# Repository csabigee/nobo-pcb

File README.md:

# nobo-pcb
PCB design files for the nobo thermostat

Designed in KiCad

very simple schematic:

https://github.com/csabigee/nobo-pcb/assets/96885207/b5cf36cf-c3b2-4169-932b-3addc52b22ec

Links:
------------------------
 
[:mag: Reverse engineering the protocol :mag_right:](https://github.com/csabigee/nobo/wiki/Home)

[:hammer_and_wrench: Building the custom thermostat :hammer_and_wrench:](https://www.hackster.io/csabigee/nobo-wireless-thermostat-01f106)

[:zap: PCB design files :zap:](https://github.com/csabigee/nobo-pcb)

[:gift: Enclosure design files :gift:](https://github.com/csabigee/nobo-enclosure)

[:octocat: Software sources :octocat:](https://github.com/csabigee/nobo)

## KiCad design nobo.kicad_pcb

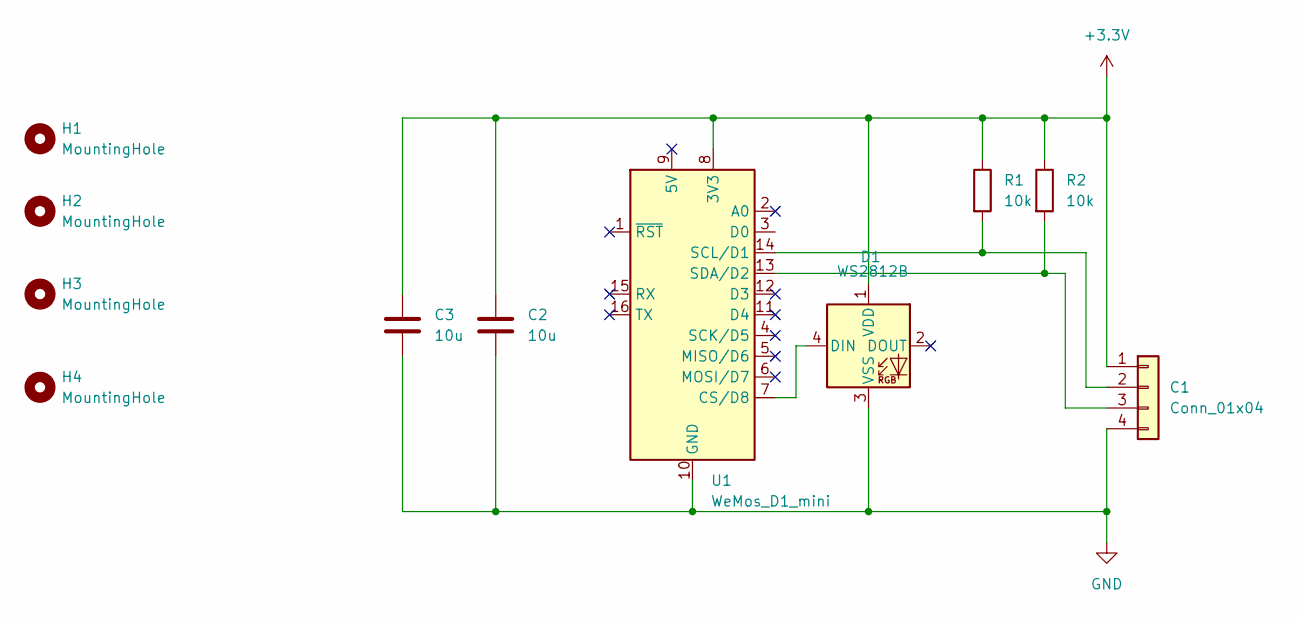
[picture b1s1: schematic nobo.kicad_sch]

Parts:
C1: Conn_01x04; nobo
C2, C3: 10u; C_0603_1608Metric_Pad1.08x0.95mm_HandSolder
D1: WS2812B; LED_WS2812B_PLCC4_5.0x5.0mm_P3.2mm
H1, H2, H3, H4: MountingHole; MountingHole_3.7mm
R1, R2: 10k; R_0603_1608Metric_Pad0.98x0.95mm_HandSolder
U1: WeMos_D1_mini; WEMOS_D1_mini_light2

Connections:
+3.3V: C1.1 (Pin_1_(3.3V)), C2.1, C3.1, D1.1 (VDD), R1.1, R2.1, U1.8 (3V3); also elsewhere on the board
GND: C1.4 (Pin_4_(GND)), C2.2, C3.2, D1.3 (VSS), U1.10 (GND); also elsewhere on the board
unnamed 2: C1.2 (Pin_2_(SCL)), R1.2, U1.14 (SCL/D1); also elsewhere on the board
unnamed 3: C1.3 (Pin_3_(SDA)), R2.2, U1.13 (SDA/D2); also elsewhere on the board
unnamed: D1.4 (DIN), U1.7 (CS/D8)

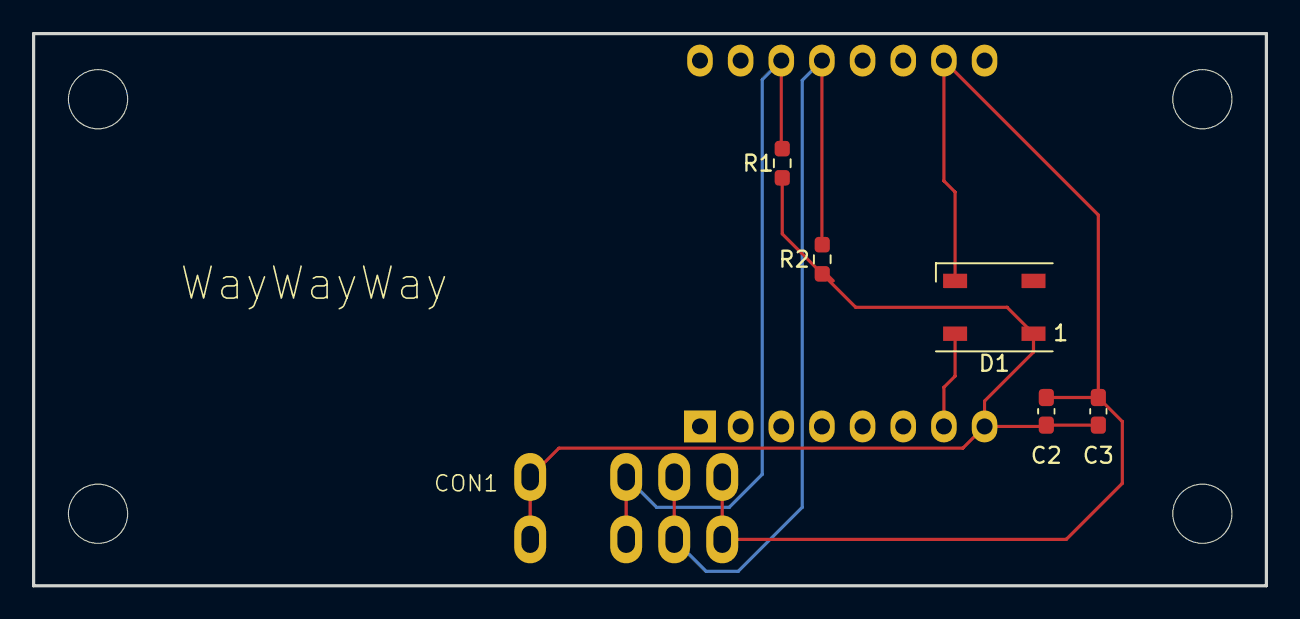
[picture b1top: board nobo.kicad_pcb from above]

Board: 2 copper layers, 77.0 x 34.5 mm, 11 parts (1 on the bottom side), 5 nets.

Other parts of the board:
CON1: Conn_01x04; nobo

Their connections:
+3.3V: CON1.1 (Pin_1_(3.3V)); also elsewhere on the board
GND: CON1.4 (Pin_4_(GND)); also elsewhere on the board
unnamed 2: CON1.2 (Pin_2_(SCL)); also elsewhere on the board
unnamed 3: CON1.3 (Pin_3_(SDA)); also elsewhere on the board

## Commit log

2024-06-22 initial version
2024-06-22 Create LICENSE
2024-06-22 Update LICENSE
